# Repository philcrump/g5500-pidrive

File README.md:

# G-5500 PiDrive

***This project is a work in progress, very little testing has so far been done, I supply no guarantee that the basic concepts work***

Controlling an AC-type Yaesu G-5500 Az+El Rotator with PWM from a Raspberry Pi, allowing a portable and compact drive unit running off a 12V battery with no mains inverters.

Choices have been made to use high-end voltage-isolated parts to allow easy co-existence with multiple power domains, as several RF receivers will also be connected to the Raspberry Pi.

## Physical Form Factor

PWM board intends to mount on the _back_ of an RPI DIN Plate, facing the Host Raspberry Pi on another DIN plate, connected by Adafruit GPIO Ribbon Cable.
* https://thepihut.com/products/dinrplate-2-raspberry-pi-din-rail-mount

PCB Render:

### Supply Voltage

36-48V Input, Tracpower Isolated TEL 12-4811WI DC-DC converts down to 5.1V @ 2.4A for the Raspberry Pi.

MAX22530 12-bit Isolated ADC cam measure the input voltage, and also exposes a connector to measure 12V battery voltage, and an optional extra channel (charge current?)

## G-5500 Control

### Motor Drive

Yaesu mains control box produces 80V pk-pk AC. Initially I plan to use a cheap 12V -> 36V DC-DC step-up to allow output of 72V pk-pk AC. The design allows for increasing to 48V motor bus voltage.

DRV8251A 4.1A Motor drivers used to achieve 50Hz AC PWM over the relevant winding for each direction. Initial experiments with variable-frequency were not very successful, but there may be +/-10% to play with for accel/decel softening.

E-STOP implemented with hardware logic (high-speed CMOS) holds motors in 'Brake' regardless of software - if switch contact is opened.

Footprints have been included to allow the use of RF chokes on the PWM outputs if RFI problems are encountered.

### Potentiometer sensing

MCP3202 12-bit ADC measures the wiper voltage on each of the Az+El Potentiometers to sense position. Careful decoupling of the supply voltage and filtering of the wiper voltage is implemented to achieve a low-noise result.

## Position / Alignment Sensors

* Uputronics Ublox GPS Breakout as daughterboard for Time + Position https://store.uputronics.com/index.php?route=product/product&path=64&product_id=84
* * Connection for NTPD Timing setup with PPS https://austinsnerdythings.com/2021/04/19/microsecond-accurate-ntp-with-a-raspberry-pi-and-pps-gps/

* BNO055 DOF IMU Fusion for magnetic-north calibration https://thepihut.com/products/adafruit-9-dof-absolute-orientation-imu-fusion-breakout-bno055
* * Mounted at end of aluminium boom
* * Active I2C LTC4311 Terminator to extend the I2C far enough down the boom (screened cable will be used.)

## Software

Motor drive using pigpio's excellent ability to run hardware-timed PWM on every GPIO. https://abyz.me.uk/rpi/pigpio/index.html

## Tests

* Body diode clamping of high-z driver on other pole is enough to prevent motion of AC motor.
* Heatsinking of existing drivers is very inadequate. (Blown EL_B1/EL_B2 )
* * Added DIY copper tab heatsinks to both side of PCB
* 22R resistor between 48V & 5V ground domains had approx 1V across it (~50mA)
* * Removed & shorted out.

* Pi Running: 0.07A @ 48V
* 1x Motor drive: 0.67A @ 48V

For attachment to mast pole: https://www.ebay.co.uk/itm/265428394116

ebay wire is 16awg 1.5mm^2

12-48V: https://uk.rs-online.com/web/p/dc-dc-converters/1757784

M3.5 ring terminals for meanwell 12v mains PSU   https://uk.rs-online.com/web/p/ring-terminals/0534222

## Authors

* Phil Crump M0DNY <phil@philcrump.co.uk>

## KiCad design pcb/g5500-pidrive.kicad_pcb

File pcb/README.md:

1x LTC4311 SOT-323-5

4x DRV8251A

4x 8X11.5mm LS:5mm   82uF 63V     667-EEU-FR1J820B 

Ferrites:
0805 40mohm 3A     652-MH2029-800Y

1x 579-MCP3202BISN MCP3202 B-grade SOIC

1x MAX22530AWE+ Isolated ADC

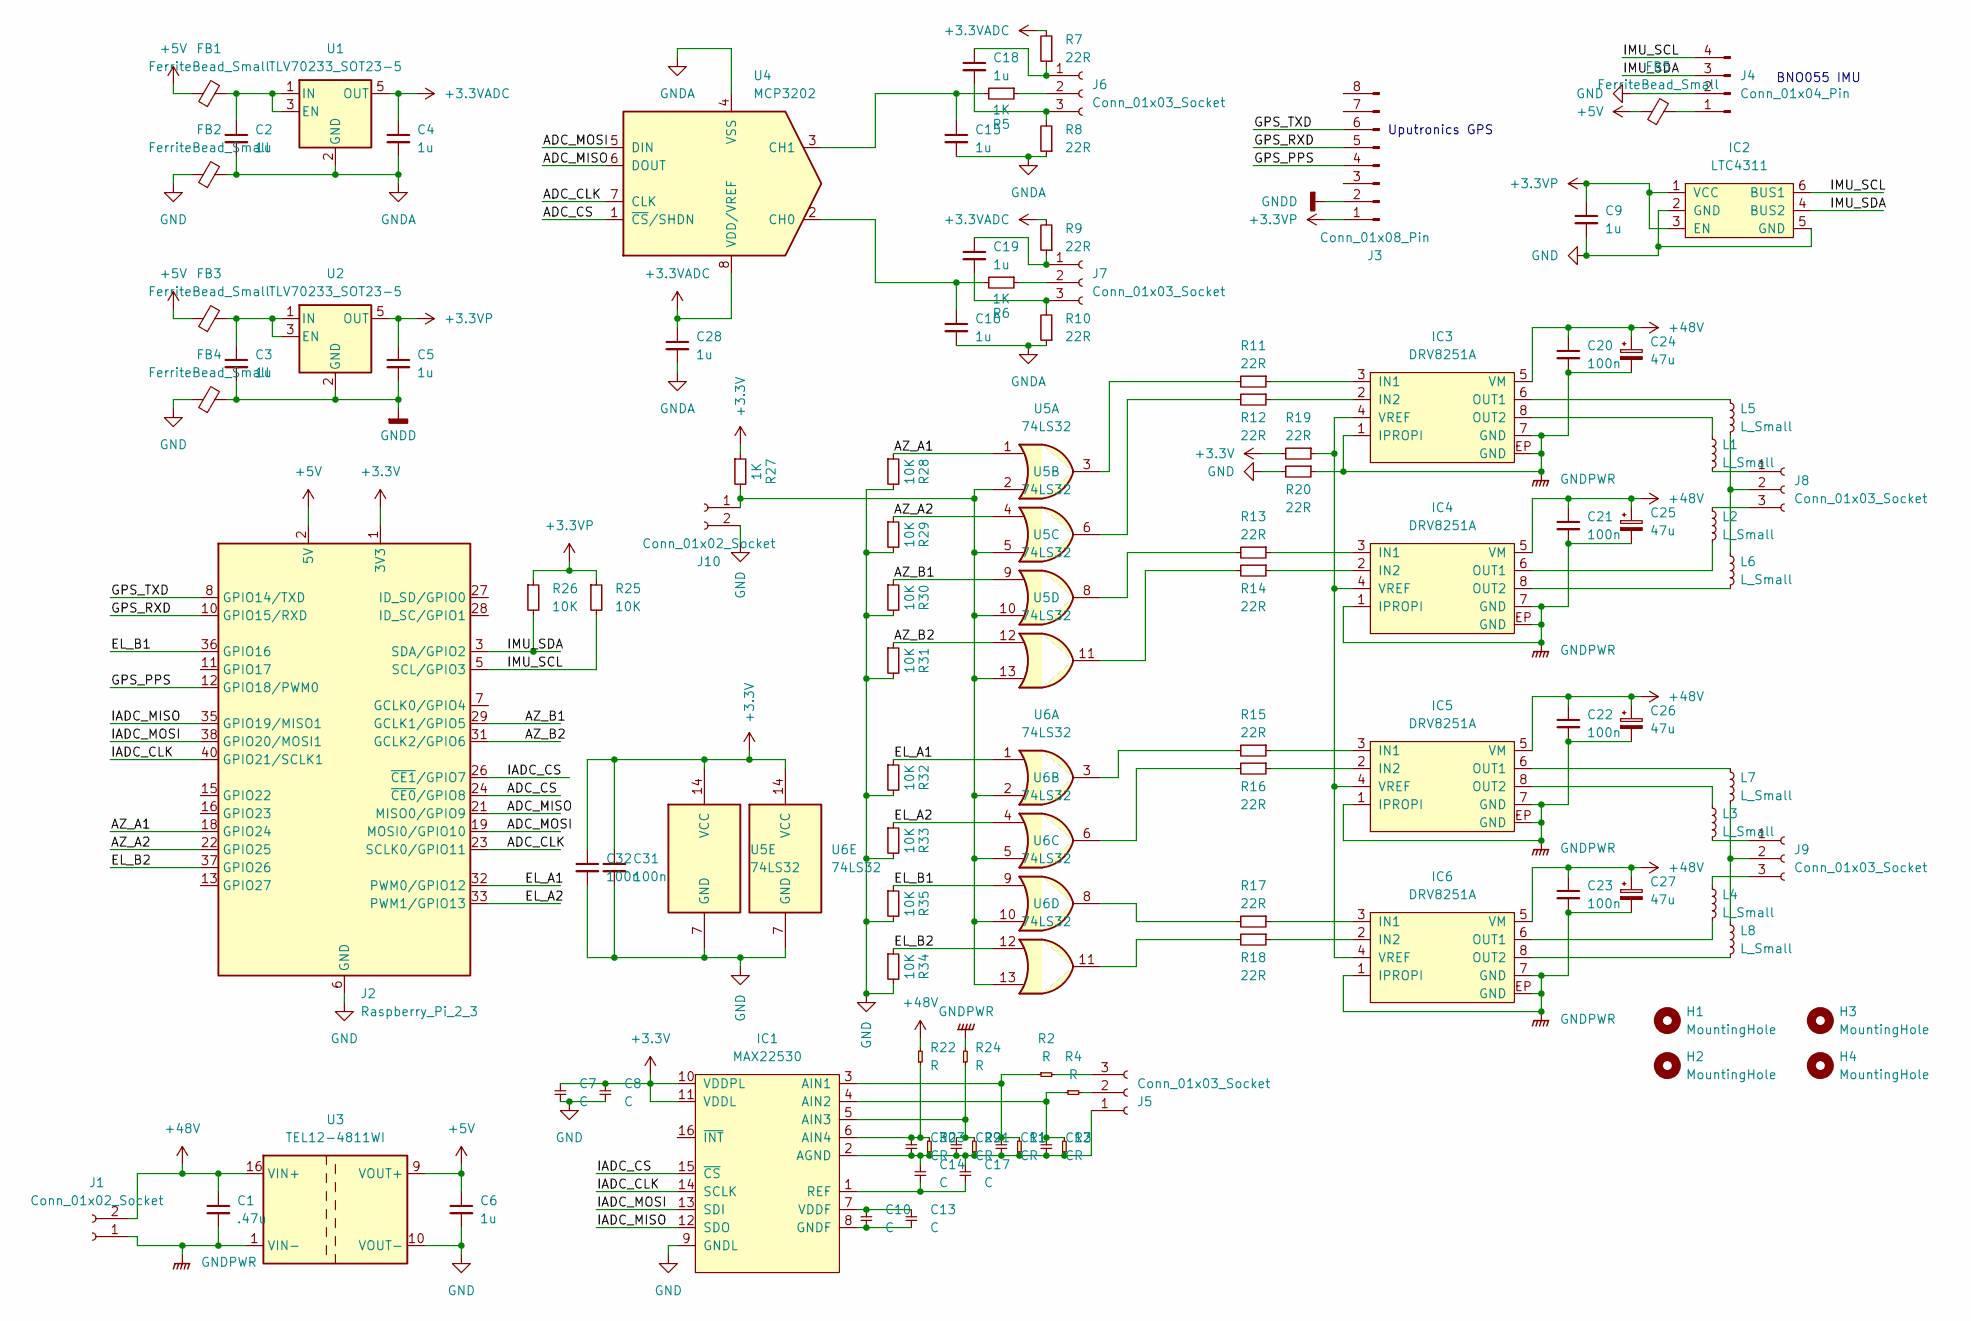
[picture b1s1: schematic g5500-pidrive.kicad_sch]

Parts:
C1: .47u; C_1206_3216Metric_Pad1.33x1.80mm_HandSolder
C2, C3, C4, C5, C6, C9, C15, C16, C18, C19, C28: 1u; C_0603_1608Metric_Pad1.08x0.95mm_HandSolder
C7, C8, C10, C11, C12, C13, C14, C17, C29, C30: C; C_0603_1608Metric_Pad1.08x0.95mm_HandSolder
C20, C21, C22, C23: 100n; C_0805_2012Metric_Pad1.18x1.45mm_HandSolder
C24, C25, C26, C27: 47u; C_Radial_D8.0mm_H11.5mm_P3.50mm
C31, C32: 100n; C_0603_1608Metric_Pad1.08x0.95mm_HandSolder
FB1, FB2, FB3, FB4, FB5: FerriteBead_Small; L_0805_2012Metric_Pad1.05x1.20mm_HandSolder
H1, H2, H3, H4: MountingHole; MountingHole_2.7mm_M2.5
IC1: MAX22530; SOIC-16-W; Mouser 700-MAX22530AWE+
IC2: LTC4311; SC-70-6; Mouser 584-C4311CSC6TRMPBF
IC3, IC4, IC5, IC6: DRV8251A; SOIC-8-EP; Mouser 595-DRV8251ADDAR
J1: Conn_01x02_Socket; TerminalBlock_RND_205-00287_1x02_P5.08mm_Horizontal
J2: Raspberry_Pi_2_3; PinSocket_2x20_P2.54mm_Vertical
J3: Conn_01x08_Pin; PinSocket_1x08_P2.54mm_Vertical
J4: Conn_01x04_Pin; PinHeader_1x04_P2.54mm_Horizontal
J5: Conn_01x03_Socket; PinHeader_1x03_P2.54mm_Horizontal
J6, J7, J8, J9: Conn_01x03_Socket; TerminalBlock_TE_282834-3_1x03_P2.54mm_Horizontal
J10: Conn_01x02_Socket; TerminalBlock_TE_282834-2_1x02_P2.54mm_Horizontal
L1, L2, L3, L4, L5, L6, L7, L8: L_Small; L_Axial_L5.3mm_D2.2mm_P10.16mm_Horizontal_Vishay_IM-1
R1, R2, R3, R4, R21, R22, R23, R24: R; R_0603_1608Metric_Pad0.98x0.95mm_HandSolder
R5, R6, R27: 1K; R_0603_1608Metric_Pad0.98x0.95mm_HandSolder
R7, R8, R9, R10, R11, R12, R13, R14, R15, R16, R17, R18, R19, R20: 22R; R_0603_1608Metric_Pad0.98x0.95mm_HandSolder
R25, R26, R28, R29, R30, R31, R32, R33, R34, R35: 10K; R_0603_1608Metric_Pad0.98x0.95mm_HandSolder
U1, U2: TLV70233_SOT23-5; SOT-23-5
U3: TEL12-4811WI; Converter_DCDC_TRACO_TEL12-xxxx_THT
U4: MCP3202; SOIC-8_3.9x4.9mm_P1.27mm
U5, U6: 74LS32; SOIC-14

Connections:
+3.3V: C7.2, C8.2, C31.1, C32.1, IC1.10 (VDDPL), IC1.11 (VDDL), J2.1 (3V3), J2.17 (3V3), R19.2, R27.1, U5.14 (VCC), U6.14 (VCC)
+3.3VADC: C4.1, C28.1, R7.2, R9.2, U1.5 (OUT), U4.8 (VDD/VREF)
+3.3VP: C5.1, C9.1, IC2.1 (VCC), IC2.3 (EN), J3.1, R25.1, R26.1, U2.5 (OUT)
+5V: C6.1, FB1.1, FB3.1, FB5.1, J2.2 (5V), J2.4 (5V), U3.9 (VOUT+)
+48V: C1.1, C20.1, C21.1, C22.1, C23.1, C24.1, C25.1, C26.1, C27.1, IC3.5 (VM), IC4.5 (VM), IC5.5 (VM), IC6.5 (VM), J1.2, R22.2, U3.16 (VIN+)
/ADC_CLK: J2.23 (SCLK0/GPIO11), U4.7 (CLK)
/ADC_CS: J2.24 (~CE0/GPIO8), U4.1 (~CS/SHDN)
/ADC_MISO: J2.21 (MISO0/GPIO9), U4.6 (DOUT)
/ADC_MOSI: J2.19 (MOSI0/GPIO10), U4.5 (DIN)
/AZ_A1: J2.18 (GPIO24), R28.1, U5.1
/AZ_A2: J2.22 (GPIO25), R29.1, U5.4
/AZ_B1: J2.29 (GCLK1/GPIO5), R30.1, U5.9
/AZ_B2: J2.31 (GCLK2/GPIO6), R31.1, U5.12
/EL_A1: J2.32 (PWM0/GPIO12), R32.1, U6.1
/EL_A2: J2.33 (PWM1/GPIO13), R33.1, U6.4
/EL_B1: J2.36 (GPIO16), R35.1, U6.9
/EL_B2: J2.37 (GPIO26), R34.1, U6.12
/GPS_PPS: J2.12 (GPIO18/PWM0), J3.4
/GPS_RXD: J2.10 (GPIO15/RXD), J3.5
/GPS_TXD: J2.8 (GPIO14/TXD), J3.6
/IADC_CLK: IC1.14 (SCLK), J2.40 (GPIO21/SCLK1)
/IADC_CS: IC1.15 (~CS), J2.26 (~CE1/GPIO7)
/IADC_MISO: IC1.12 (SDO), J2.35 (GPIO19/MISO1)
/IADC_MOSI: IC1.13 (SDI), J2.38 (GPIO20/MOSI1)
/IMU_SCL: IC2.6 (BUS1), J2.5 (SCL/GPIO3), J4.4, R25.2
/IMU_SDA: IC2.4 (BUS2), J2.3 (SDA/GPIO2), J4.3, R26.2
GND: C6.2, C7.1, C8.1, C9.2, C31.2, C32.2, FB2.1, FB4.1, IC1.9 (GNDL), IC2.2 (GND), IC2.5 (GND), J2.6 (GND), J2.9 (GND), J2.14 (GND), J2.20 (GND), J2.25 (GND), J2.30 (GND), J2.34 (GND), J2.39 (GND), J4.2, J10.2, R20.2, R28.2, R29.2, R30.2, R31.2, R32.2, R33.2, R34.2, R35.2, U3.10 (VOUT-), U5.7 (GND), U6.7 (GND)
GNDA: C2.2, C4.2, C15.2, C16.2, C28.2, FB2.2, R8.1, R10.1, U1.2 (GND), U4.4 (VSS)
GNDD: C3.2, C5.2, FB4.2, J3.2, U2.2 (GND)
GNDPWR: C1.2, C20.2, C21.2, C22.2, C23.2, C24.2, C25.2, C26.2, C27.2, IC3.1 (IPROPI), IC3.7 (GND), IC3.EP (GND), IC4.1 (IPROPI), IC4.7 (GND), IC4.EP (GND), IC5.1 (IPROPI), IC5.7 (GND), IC5.EP (GND), IC6.1 (IPROPI), IC6.7 (GND), IC6.EP (GND), J1.1, R20.1, R24.2, U3.1 (VIN-)
unnamed: C11.1, C12.1, C14.1, C17.1, C29.1, C30.1, IC1.2 (AGND), J5.1, R1.1, R3.1, R21.1, R23.1
unnamed: C11.2, IC1.3 (AIN1), R1.2, R2.1
unnamed: C12.2, IC1.4 (AIN2), R3.2, R4.1
unnamed: C29.2, IC1.5 (AIN3), R21.2, R24.1
unnamed: C30.2, IC1.6 (AIN4), R22.1, R23.2
unnamed: C10.1, C13.1, IC1.8 (GNDF)
unnamed: C14.2, C17.2, IC1.1 (REF)
unnamed: C10.2, C13.2, IC1.7 (VDDF)
unnamed: IC3.3 (IN1), R11.1
unnamed: IC3.2 (IN2), R12.1
unnamed: IC3.6 (OUT1), L5.1
unnamed: IC3.8 (OUT2), L1.1
unnamed: IC3.4 (VREF), IC4.4 (VREF), IC5.4 (VREF), IC6.4 (VREF), R19.1
unnamed: IC4.3 (IN1), R13.1
unnamed: IC4.2 (IN2), R14.1
unnamed: IC4.6 (OUT1), L2.2
unnamed: IC4.8 (OUT2), L6.2
unnamed: IC5.3 (IN1), R15.1
unnamed: IC5.2 (IN2), R16.1
unnamed: IC5.6 (OUT1), L7.1
unnamed: IC5.8 (OUT2), L3.1
unnamed: IC6.3 (IN1), R17.1
unnamed: IC6.2 (IN2), R18.1
unnamed: IC6.6 (OUT1), L4.2
unnamed: IC6.8 (OUT2), L8.2
unnamed: FB5.2, J4.1
unnamed: J5.2, R4.2
unnamed: J5.3, R2.2
unnamed: C18.1, J6.1, R7.1
unnamed: J6.2, R5.1
unnamed: C18.2, J6.3, R8.2
unnamed: C19.1, J7.1, R9.1
unnamed: J7.2, R6.1
unnamed: C19.2, J7.3, R10.2
unnamed: J8.1, L1.2
unnamed: J8.2, L5.2, L6.1
unnamed: J8.3, L2.1
unnamed: J9.1, L3.2
unnamed: J9.2, L7.2, L8.1
unnamed: J9.3, L4.1
unnamed: J10.1, R27.2, U5.2, U5.5, U5.10, U5.13, U6.2, U6.5, U6.10, U6.13
unnamed: R11.2, U5.3
unnamed: R12.2, U5.6
unnamed: R13.2, U5.8
unnamed: R14.2, U5.11
unnamed: R15.2, U6.3
unnamed: R16.2, U6.6
unnamed: R17.2, U6.8
unnamed: R18.2, U6.11
unnamed: C2.1, FB1.2, U1.1 (IN), U1.3 (EN)
unnamed: C3.1, FB3.2, U2.1 (IN), U2.3 (EN)
unnamed: C16.1, R6.2, U4.2 (CH0)
unnamed: C15.1, R5.2, U4.3 (CH1)

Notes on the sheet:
Uputronics GPS
BNO055 IMU

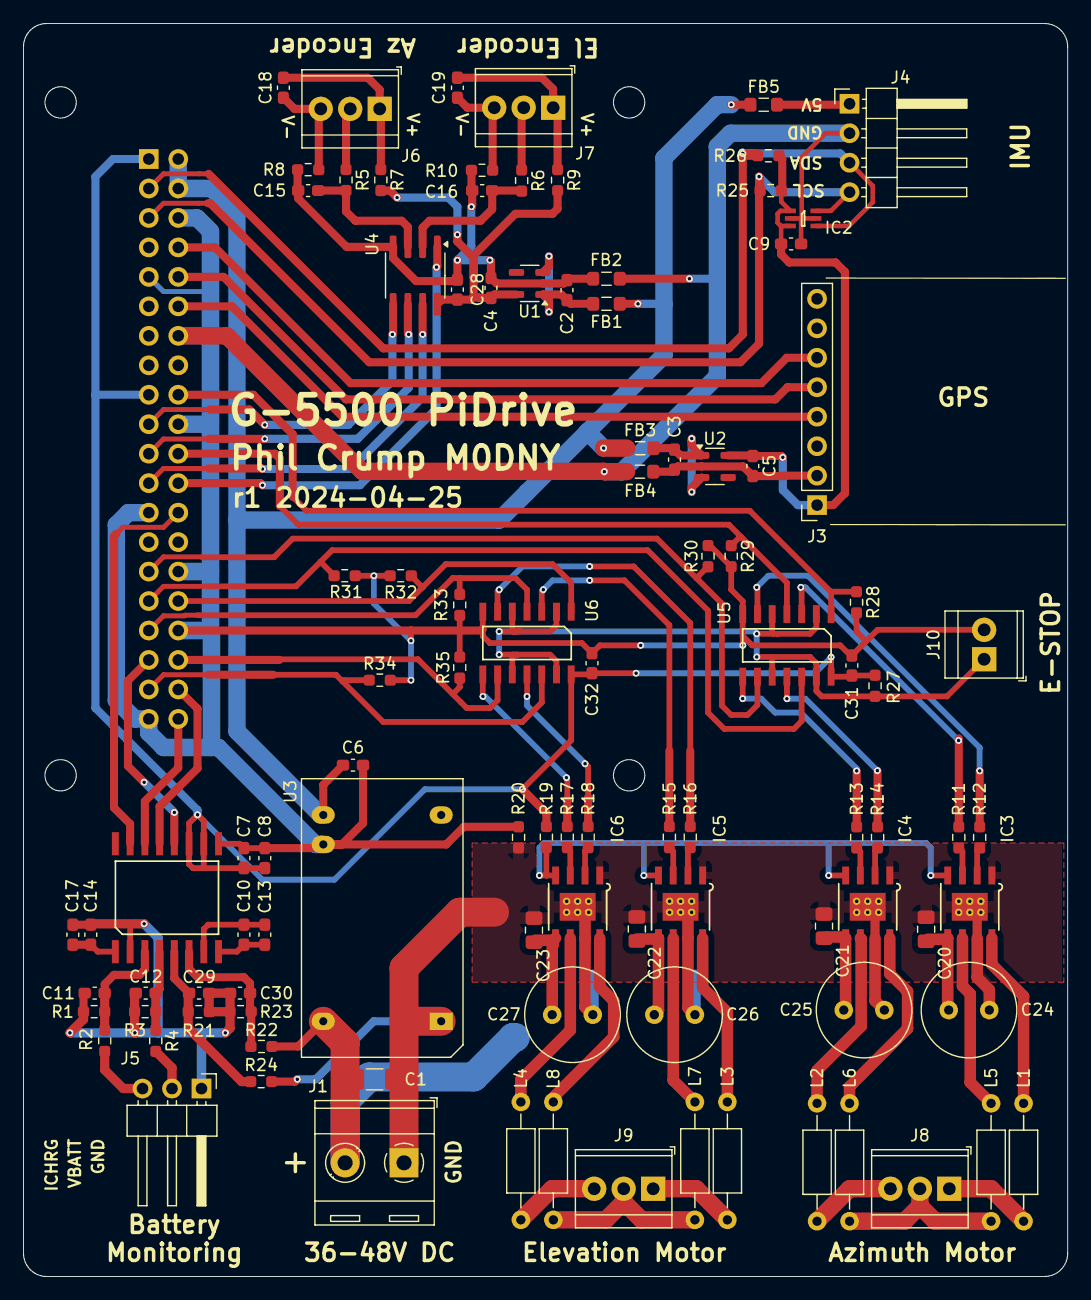
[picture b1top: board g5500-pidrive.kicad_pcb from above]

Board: 2 copper layers, 90.0 x 108.0 mm, 106 parts (1 on the bottom side), 83 nets.

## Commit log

2024-04-25 Initial Commit.
2024-08-12 Add libpredict + libwebsockets submodules.
2024-08-12 Add software progress.
2024-08-15 README.md: Add testing notes.
